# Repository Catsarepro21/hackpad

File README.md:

# hackpad

This is a "hackpad" for Stardance Hack Club!
Its current fuctions are to run commands such as git commit to make coding quicker and more satisfying.

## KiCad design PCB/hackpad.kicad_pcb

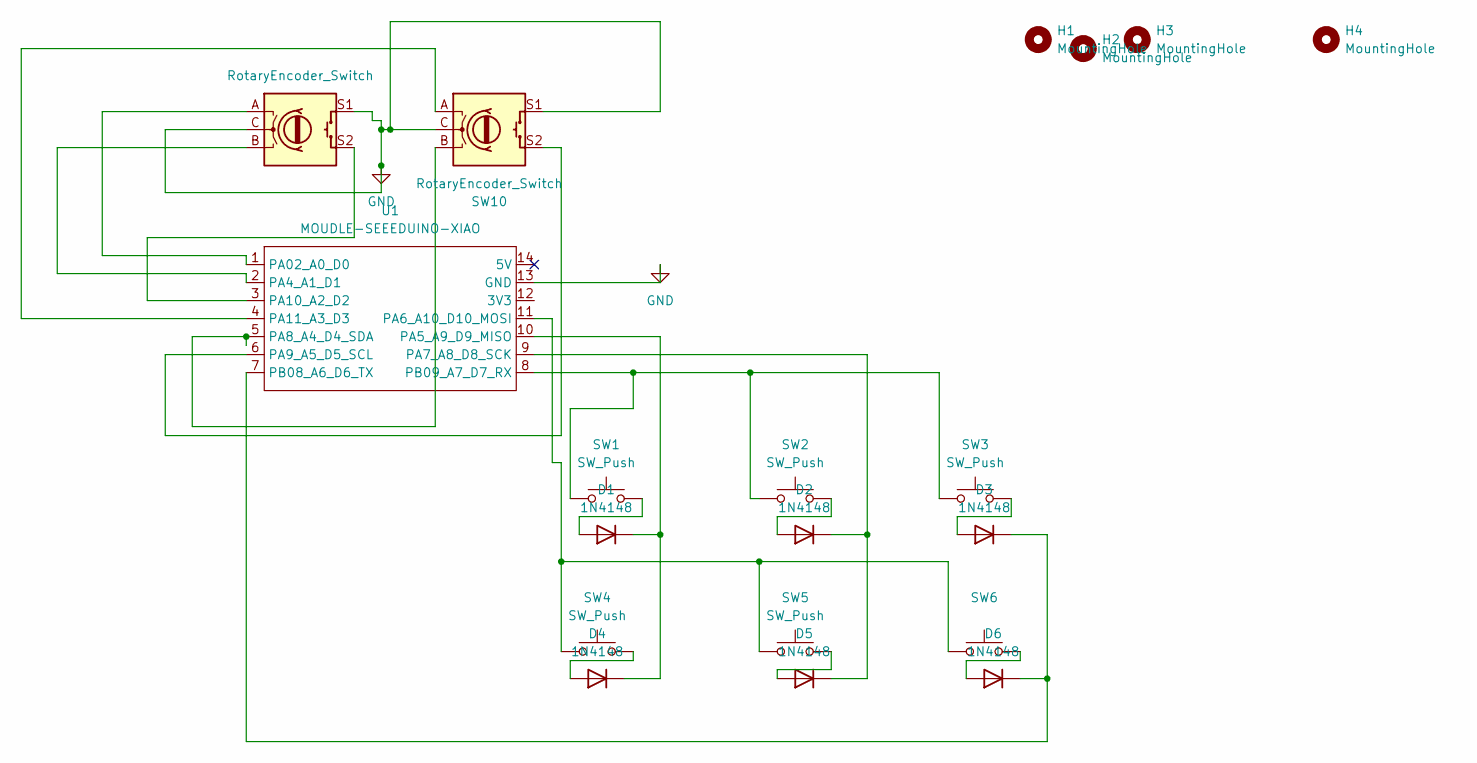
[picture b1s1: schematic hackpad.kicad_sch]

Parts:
D1, D2, D3, D4, D5, D6: 1N4148; D_DO-35_SOD27_P7.62mm_Horizontal
H1, H2, H3, H4: MountingHole; MountingHole_3.2mm_M3
SW1, SW2, SW3, SW4, SW5, SW6: SW_Push; SW_Cherry_MX_1.00u_PCB
SW9, SW10: RotaryEncoder_Switch; RotaryEncoder_Alps_EC11E-Switch_Vertical_H20mm
U1: MOUDLE-SEEEDUINO-XIAO; XIAO-Generic-Hybrid-14P-2.54-21X17.8MM

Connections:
GND: SW9.C, SW9.S1, SW10.C, SW10.S1, U1.13 (GND)
unnamed: D1.2 (A), SW1.2
unnamed: D1.1 (K), D4.1 (K), U1.10 (PA5_A9_D9_MISO)
unnamed: D2.2 (A), SW2.2
unnamed: D2.1 (K), D5.1 (K), U1.9 (PA7_A8_D8_SCK)
unnamed: D3.2 (A), SW3.2
unnamed: D3.1 (K), D6.1 (K), U1.7 (PB08_A6_D6_TX)
unnamed: D4.2 (A), SW4.2
unnamed: D5.2 (A), SW5.2
unnamed: D6.2 (A), SW6.2
unnamed: SW9.A, U1.1 (PA02_A0_D0)
unnamed: SW9.B, U1.2 (PA4_A1_D1)
unnamed: SW4.1, SW5.1, SW6.1, U1.11 (PA6_A10_D10_MOSI)
unnamed: SW10.B, U1.5 (PA8_A4_D4_SDA)
unnamed: SW10.S2, U1.6 (PA9_A5_D5_SCL)
unnamed: SW9.S2, U1.3 (PA10_A2_D2)
unnamed: SW10.A, U1.4 (PA11_A3_D3)
unnamed: SW1.1, SW2.1, SW3.1, U1.8 (PB09_A7_D7_RX)

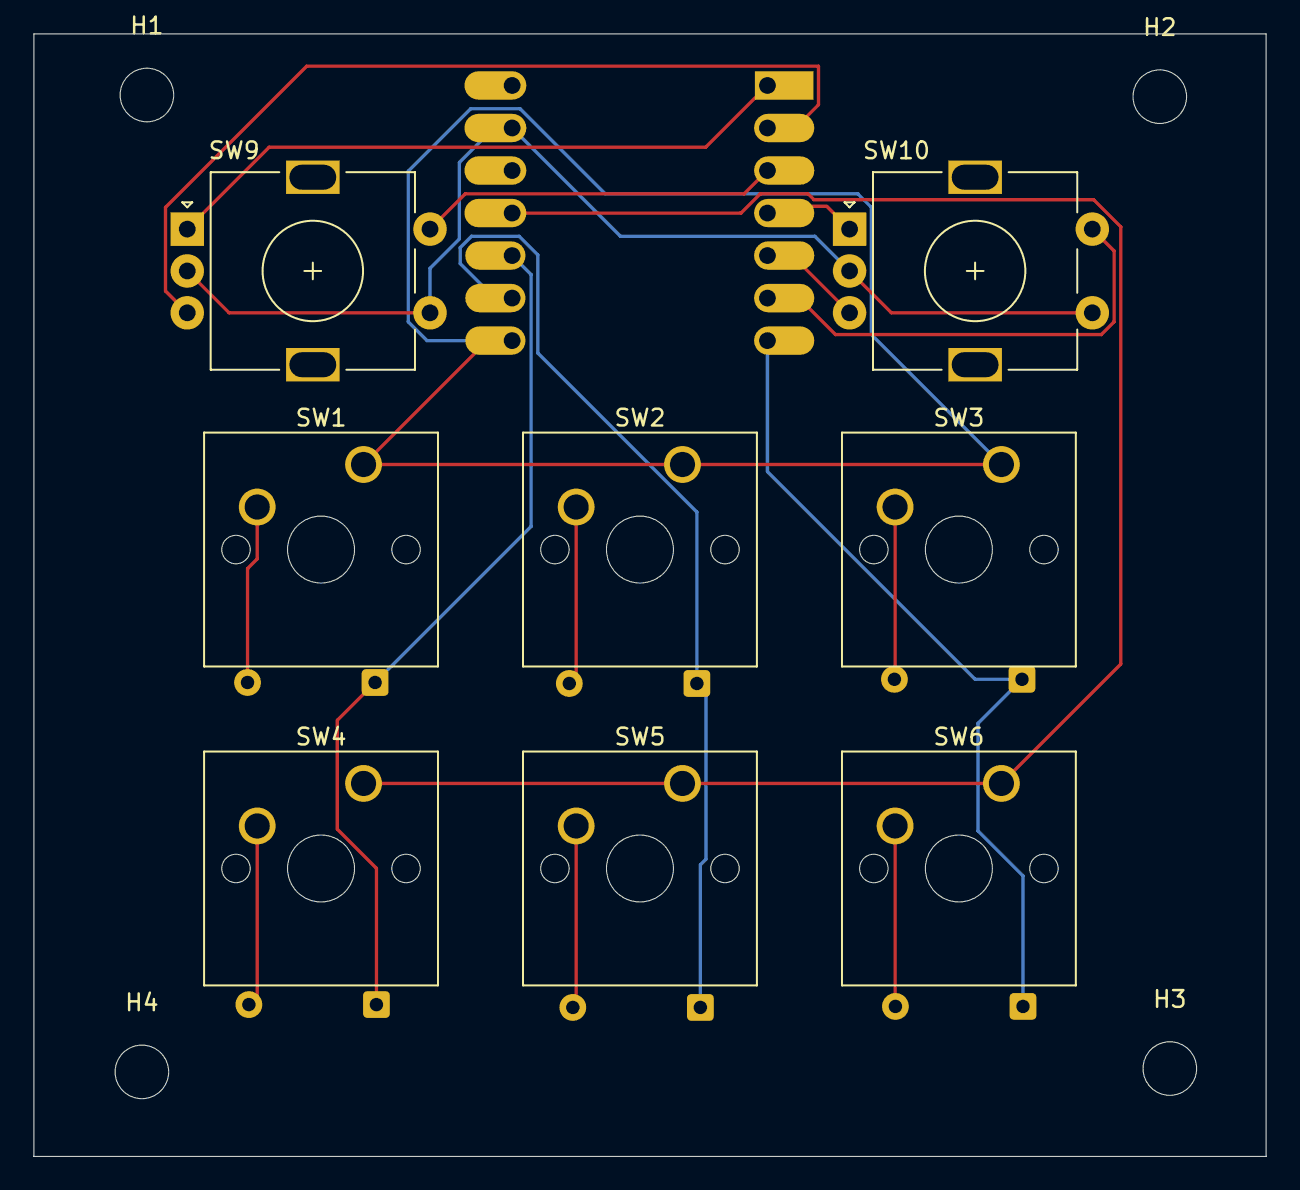
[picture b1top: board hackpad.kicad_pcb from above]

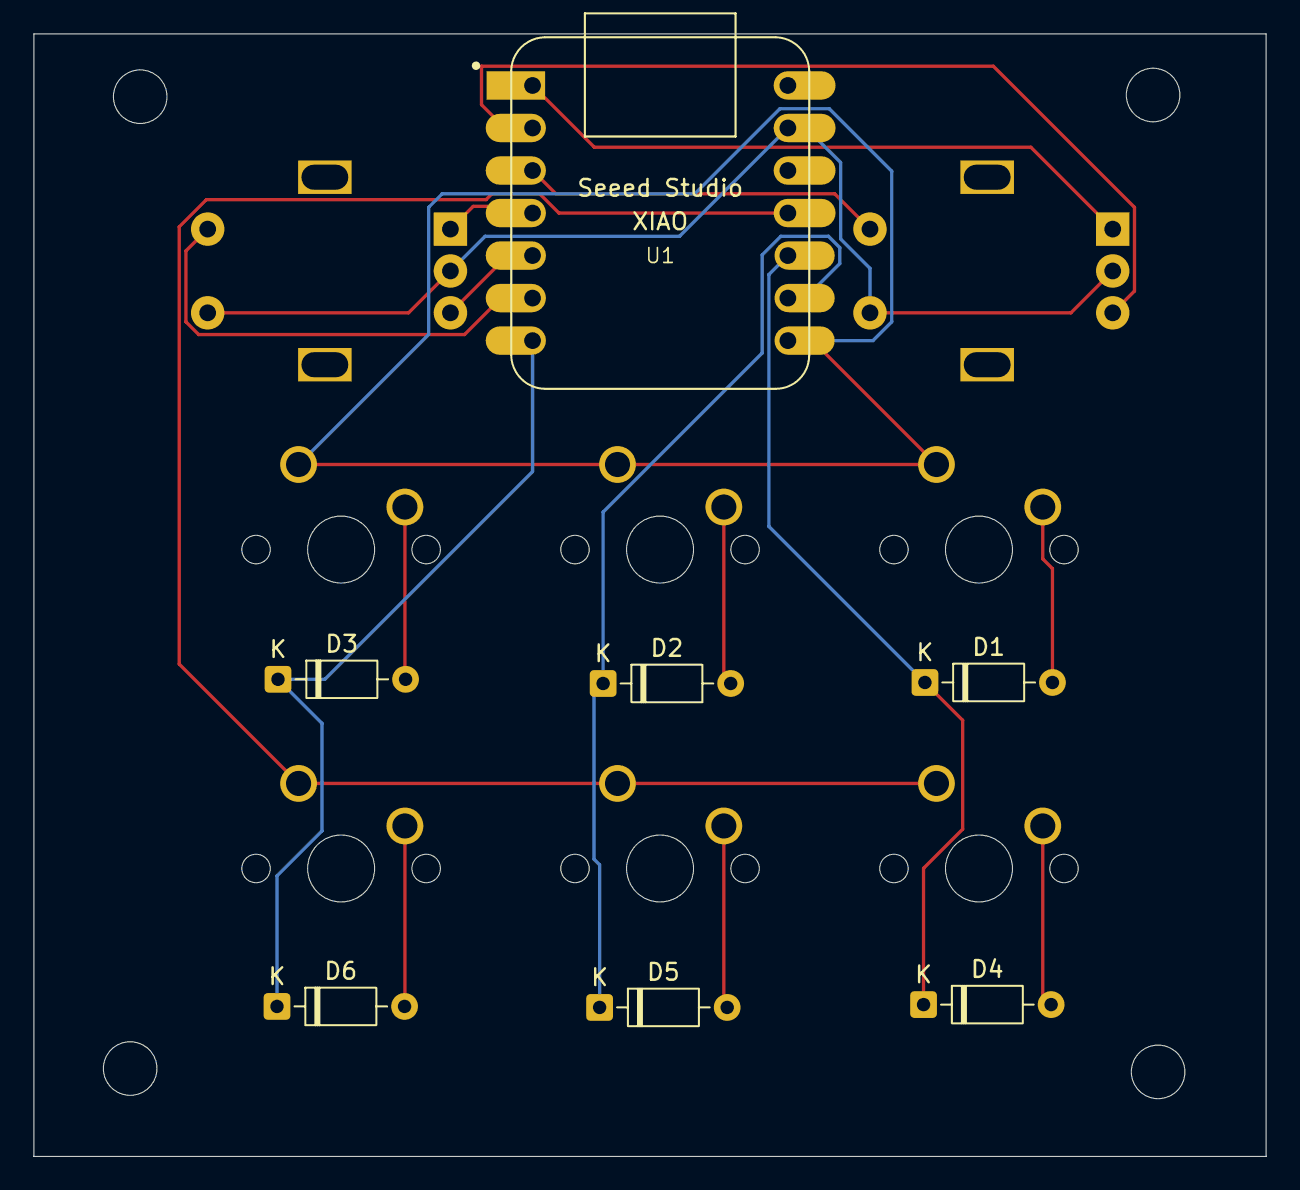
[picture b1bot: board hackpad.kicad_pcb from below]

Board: 2 copper layers, 73.6 x 67.1 mm, 19 parts (7 on the bottom side), 18 nets.

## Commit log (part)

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2026-06-09 Uploaded all main files
